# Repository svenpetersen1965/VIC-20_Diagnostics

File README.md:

# VIC-20_Diagnostics
This is a diagnostic  harness and the description of the diagnostic cartridge for the Commodore VIC-20, based on the original Commodore diagnostic harness and software.

The Diagnostic Cartridge is based on the design for the <a href="https://github.com/svenpetersen1965/Commodore-VIC-20-Super-Expander-II">VIC-20 Super Expander II</a> design.

Alternatively, the <a href="https://github.com/svenpetersen1965/VIC-20-Hyper-Expander">Hyper Expander</a> Cartridge can be used as a Diagnostic cartridge, too. All RAM (except the BLK5 8K block) can be installed for the Diagnostic.  

The general description of the VIC-20 Diagnostics can be found in the "Top-Level Project" folder.

The Rev. 1 of the User Port PCB just has a reduced part count.and a new logo.

Please find the (C64) cassette port adapter <a href="https://github.com/svenpetersen1965/C64-Diagnostic-Rev.-586220-Harness/tree/master/Diag586220_Harness/Diag586220_Cassette_Port">here</a>.

Please also refer to <a href="http://tech.guitarsite.de/vic-20_diagnostics.html">my website</a>

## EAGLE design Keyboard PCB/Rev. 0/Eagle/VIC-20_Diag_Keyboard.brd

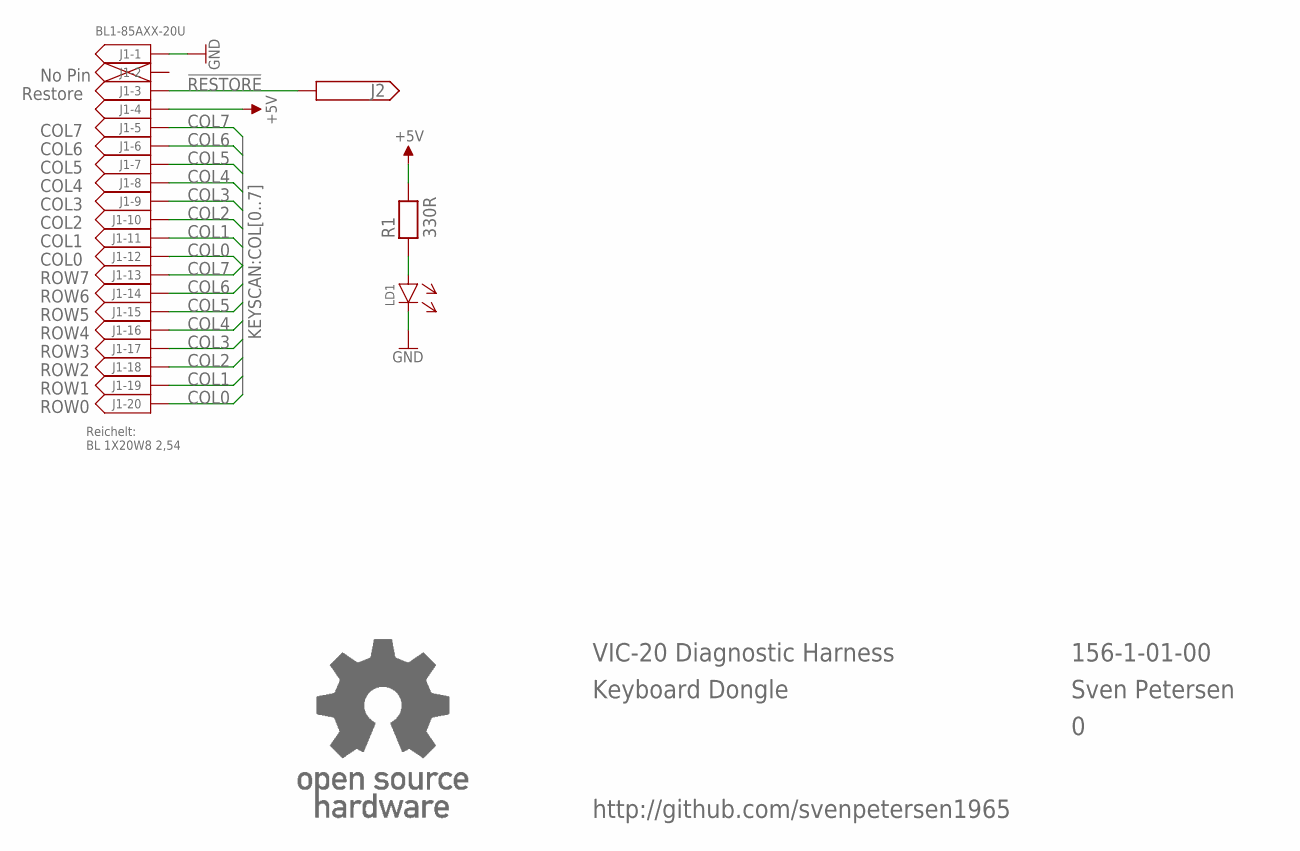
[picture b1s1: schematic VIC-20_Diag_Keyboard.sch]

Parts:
J1: BL1-85AXX-20U
J2: PINHD-1X1; 1X01
LD1: 3MM
R1: 330R; R-10
U$9: OPEN_SOURCE_HW; OPENHW

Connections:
!RESTORE: J1.3, J2.1
+5V: J1.4, R1.2
COL0: J1.12, J1.20
COL1: J1.11, J1.19
COL2: J1.10, J1.18
COL3: J1.9, J1.17
COL4: J1.8, J1.16
COL5: J1.7, J1.15
COL6: J1.6, J1.14
COL7: J1.5, J1.13
GND: J1.1, LD1.C (K)
unnamed: LD1.A, R1.1

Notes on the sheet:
COL7
COL6
COL5
COL4
COL3
COL2
COL1
COL0
ROW7
ROW6
ROW5
ROW4
ROW3
ROW2
ROW1
ROW0
No Pin
Restore
VIC-20 Diagnostic Harness
Keyboard Dongle
156-1-01-00
Sven Petersen
Reichelt: BL 1X20W8 2,54
http://github.com/svenpetersen1965

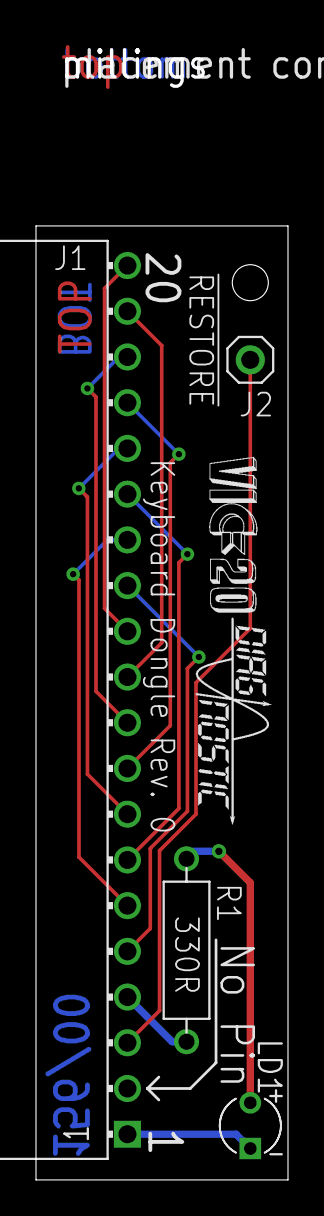
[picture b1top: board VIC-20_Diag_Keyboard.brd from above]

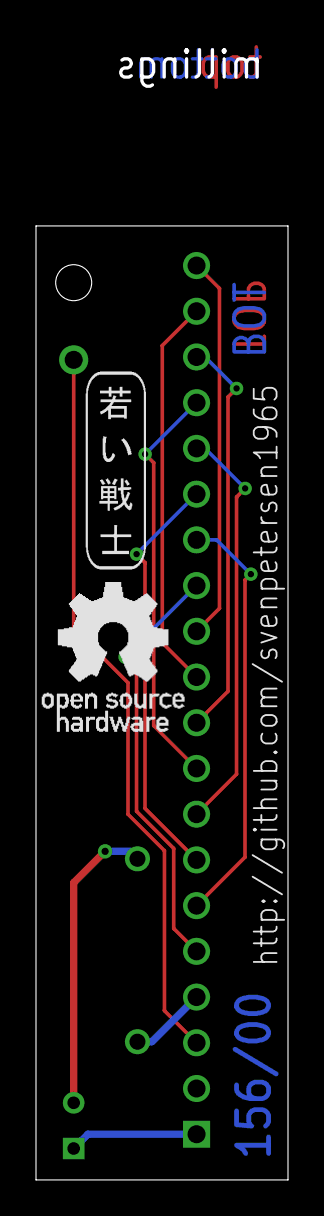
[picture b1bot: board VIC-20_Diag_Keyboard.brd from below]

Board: 2 copper layers, 14.0 x 53.0 mm, 9 parts (2 on the bottom side), 12 nets.

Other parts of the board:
U$6: 2LAYER
U$7: PCB-TITLE/
U$8: SVEN_TAG
U$10: VIC20_DIAG_SMALL

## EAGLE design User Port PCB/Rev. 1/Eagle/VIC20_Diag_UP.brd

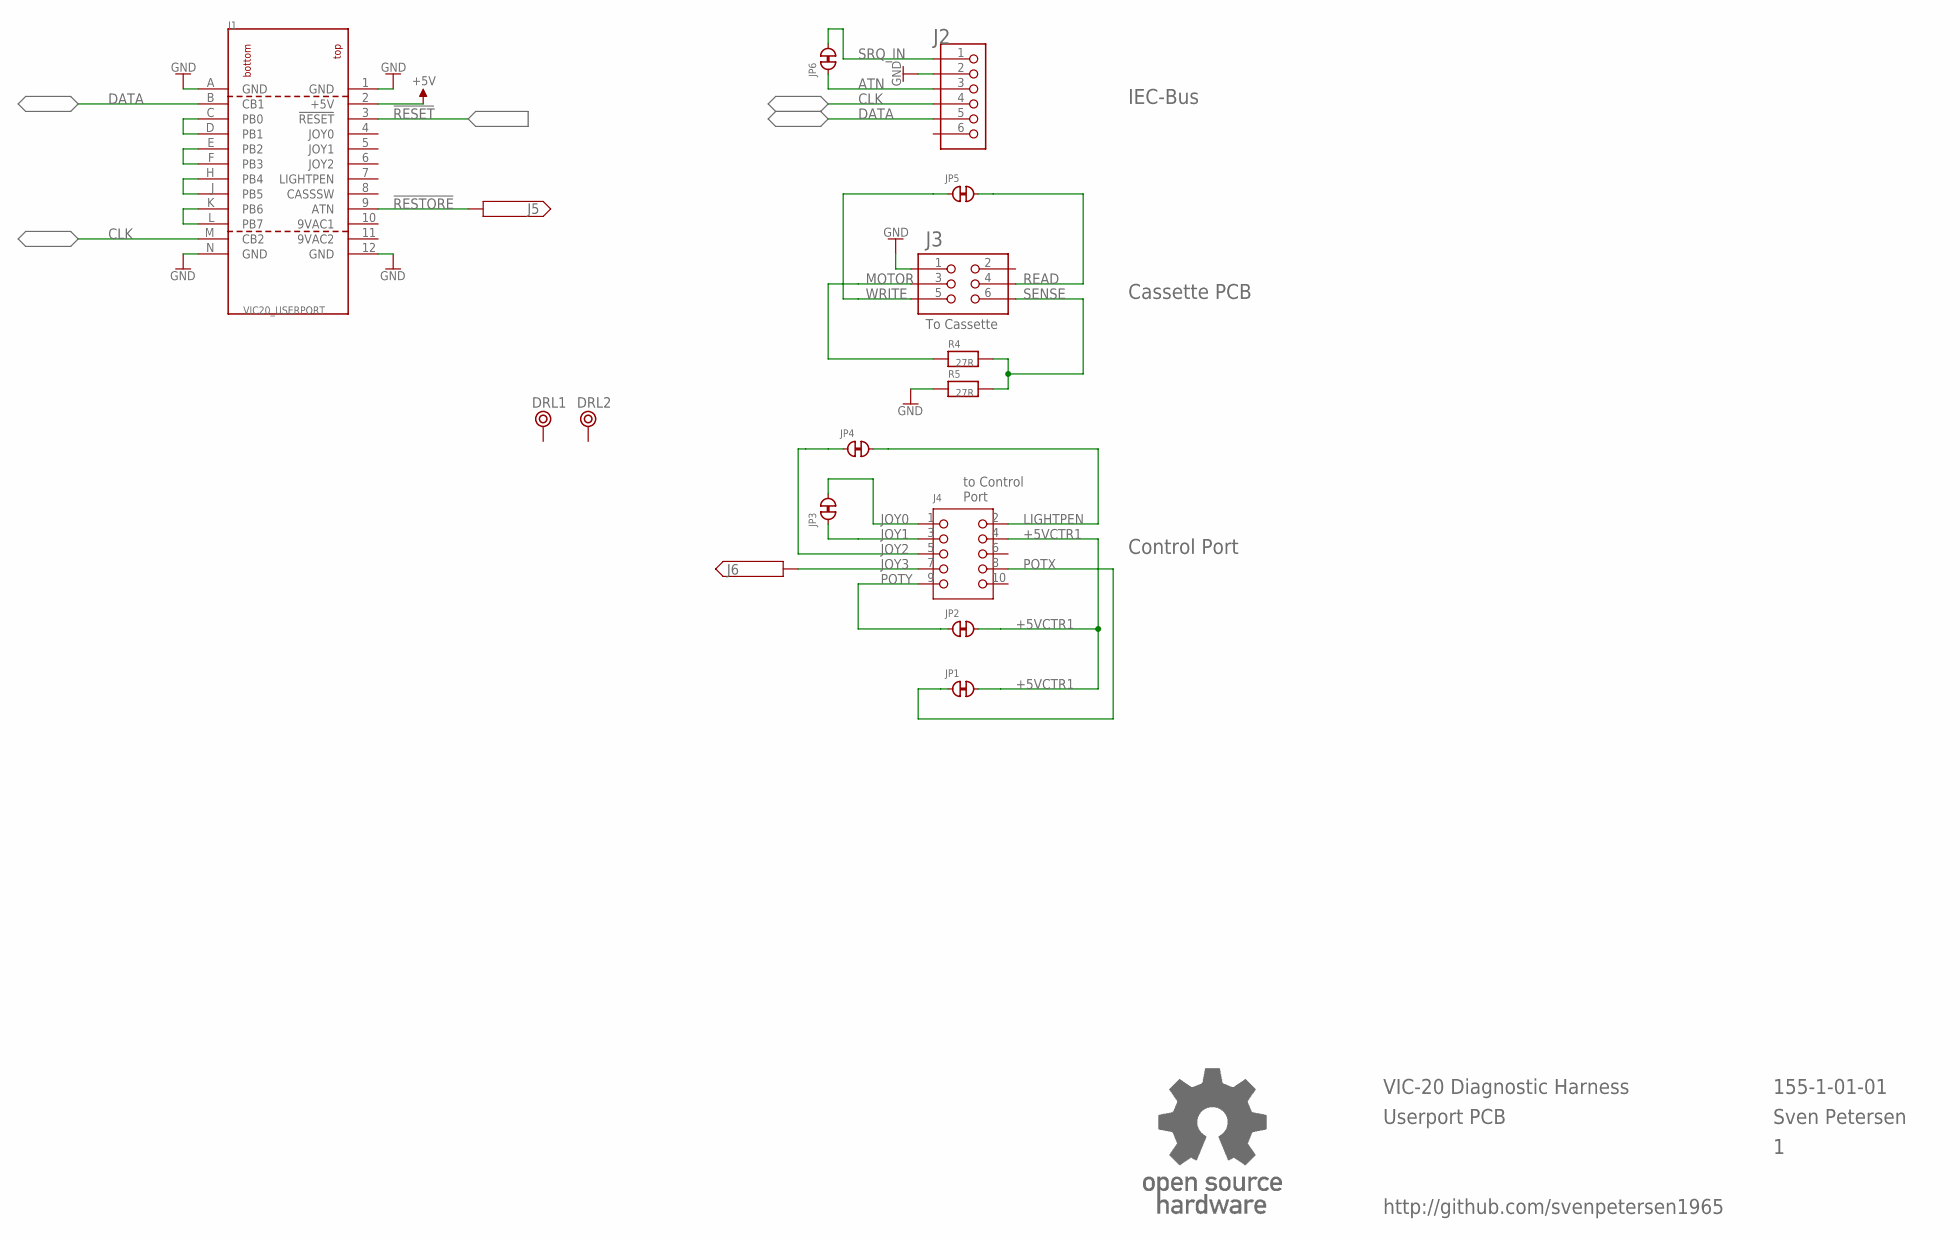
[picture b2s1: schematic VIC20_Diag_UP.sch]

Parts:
DRL1, DRL2: BOHR3,5
J1: VIC20_USERPORT; USERPORT
J2: 6410-6P
J3: 2X03WV
J4: 2X05WV
J5, J6: PINHD-1X1; 1X01
JP1, JP2, JP3, JP4, JP5, JP6: CLOSED; CP_CL
R4, R5: 27R; R-10
U$2: OPEN_SOURCE_HW; OPENHW

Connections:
9VAC1: J1.10 (9VAC1)
9VAC2: J1.11 (9VAC2)
!RESET: J1.3 (!RESET)
!RESTORE: J1.9 (ATN), J5.1
+5V: J1.2 (+5V)
+5VCTR1: J4.4, JP1.2, JP2.2
ATN: J2.3, JP6.1
CLK: J1.M (CB2), J2.4
DATA: J1.B (CB1), J2.5
GND: J1.1 (GND), J1.12 (GND), J1.A (GND), J1.N (GND), J2.2, J3.1, R5.1
JOY0: J4.1, JP3.2
JOY1: J4.3, JP3.1
JOY2: J4.5, JP4.1
JOY3: J4.7, J6.1
LIGHTPEN: J4.2, JP4.2
MOTOR: J3.3, R4.1
unnamed: J1.C (PB0), J1.D (PB1)
unnamed: J1.E (PB2), J1.F (PB3)
unnamed: J1.H (PB4), J1.J (PB5)
unnamed: J1.K (PB6), J1.L (PB7)
POTX: J4.8, JP1.1
POTY: J4.9, JP2.1
READ: J3.4, JP5.2
SENSE: J3.6, R4.2, R5.2
SRQ_IN: J2.1, JP6.2
WRITE: J3.5, JP5.1

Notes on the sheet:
To Cassette
to Control Port
155-1-01-01
Sven Petersen
VIC-20 Diagnostic Harness
Userport PCB
IEC-Bus
Cassette PCB
Control Port
http://github.com/svenpetersen1965

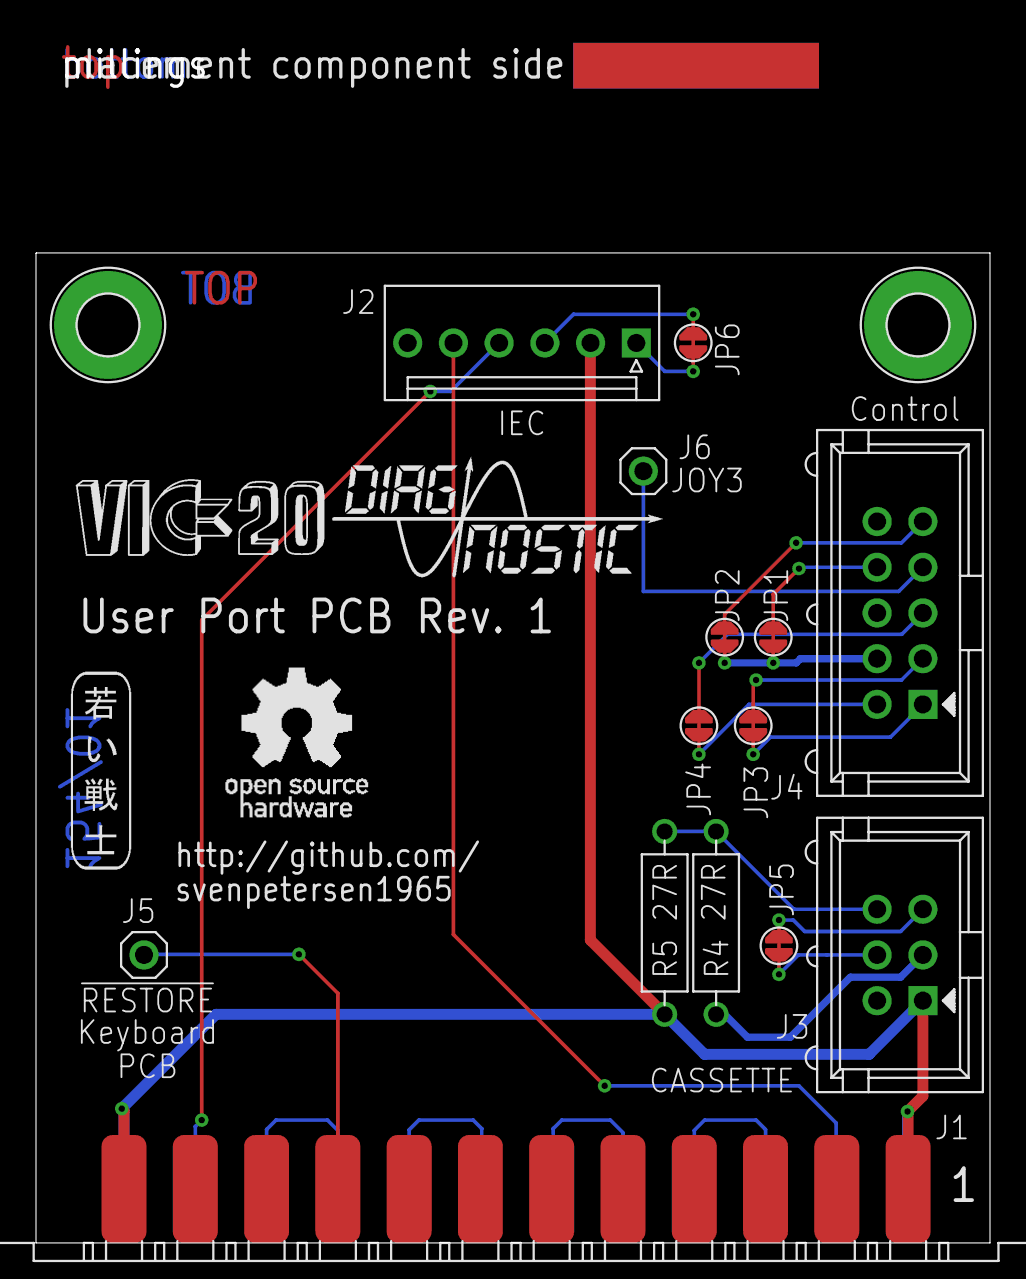
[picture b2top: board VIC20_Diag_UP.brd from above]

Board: 2 copper layers, 53.0 x 55.0 mm, 21 parts (0 on the bottom side), 22 nets.

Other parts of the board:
U$10: SVEN_TAG
U$17: PCB-TITLE/
U$18: 2LAYER
U$19: VIC20_DIAG

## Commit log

2020-10-25 Create LICENSE
2021-06-03 Added Label PNG files
2021-06-27 Mistake in the Module Description fixed
2021-07-14 Delete VIC-20_Diag_Keyboard_v0_gerber.zip
    Old version
2021-07-14 Add files via upload
    Silk Screen update
2021-07-14 Silk Screen update
2021-07-16 Rev. 1 released
    No functional update, reduced part count, new logo
2021-07-16 Silk Screen Update
    Just a new logo
2021-07-16 New logo
    Just an inkscape exercise
2021-07-16 Add files via upload
    Just a new logo
2021-08-06 New logo on silk screen
2021-08-06 New logo
2023-05-22 Delete VIC20_Diag_KB_PCB_v1.pdf
    The file was in the wrong folder.
